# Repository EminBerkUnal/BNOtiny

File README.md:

BNOtiny Breakout Board
------------------------------
Issued Date: 28 November 2023
Revision 1

This is a breakout board that I designed for a BNO08X MEMs sensor. I have designed this board to have the minimal amount of footprint possible. Board size is 48.5mm x 7.0mm.

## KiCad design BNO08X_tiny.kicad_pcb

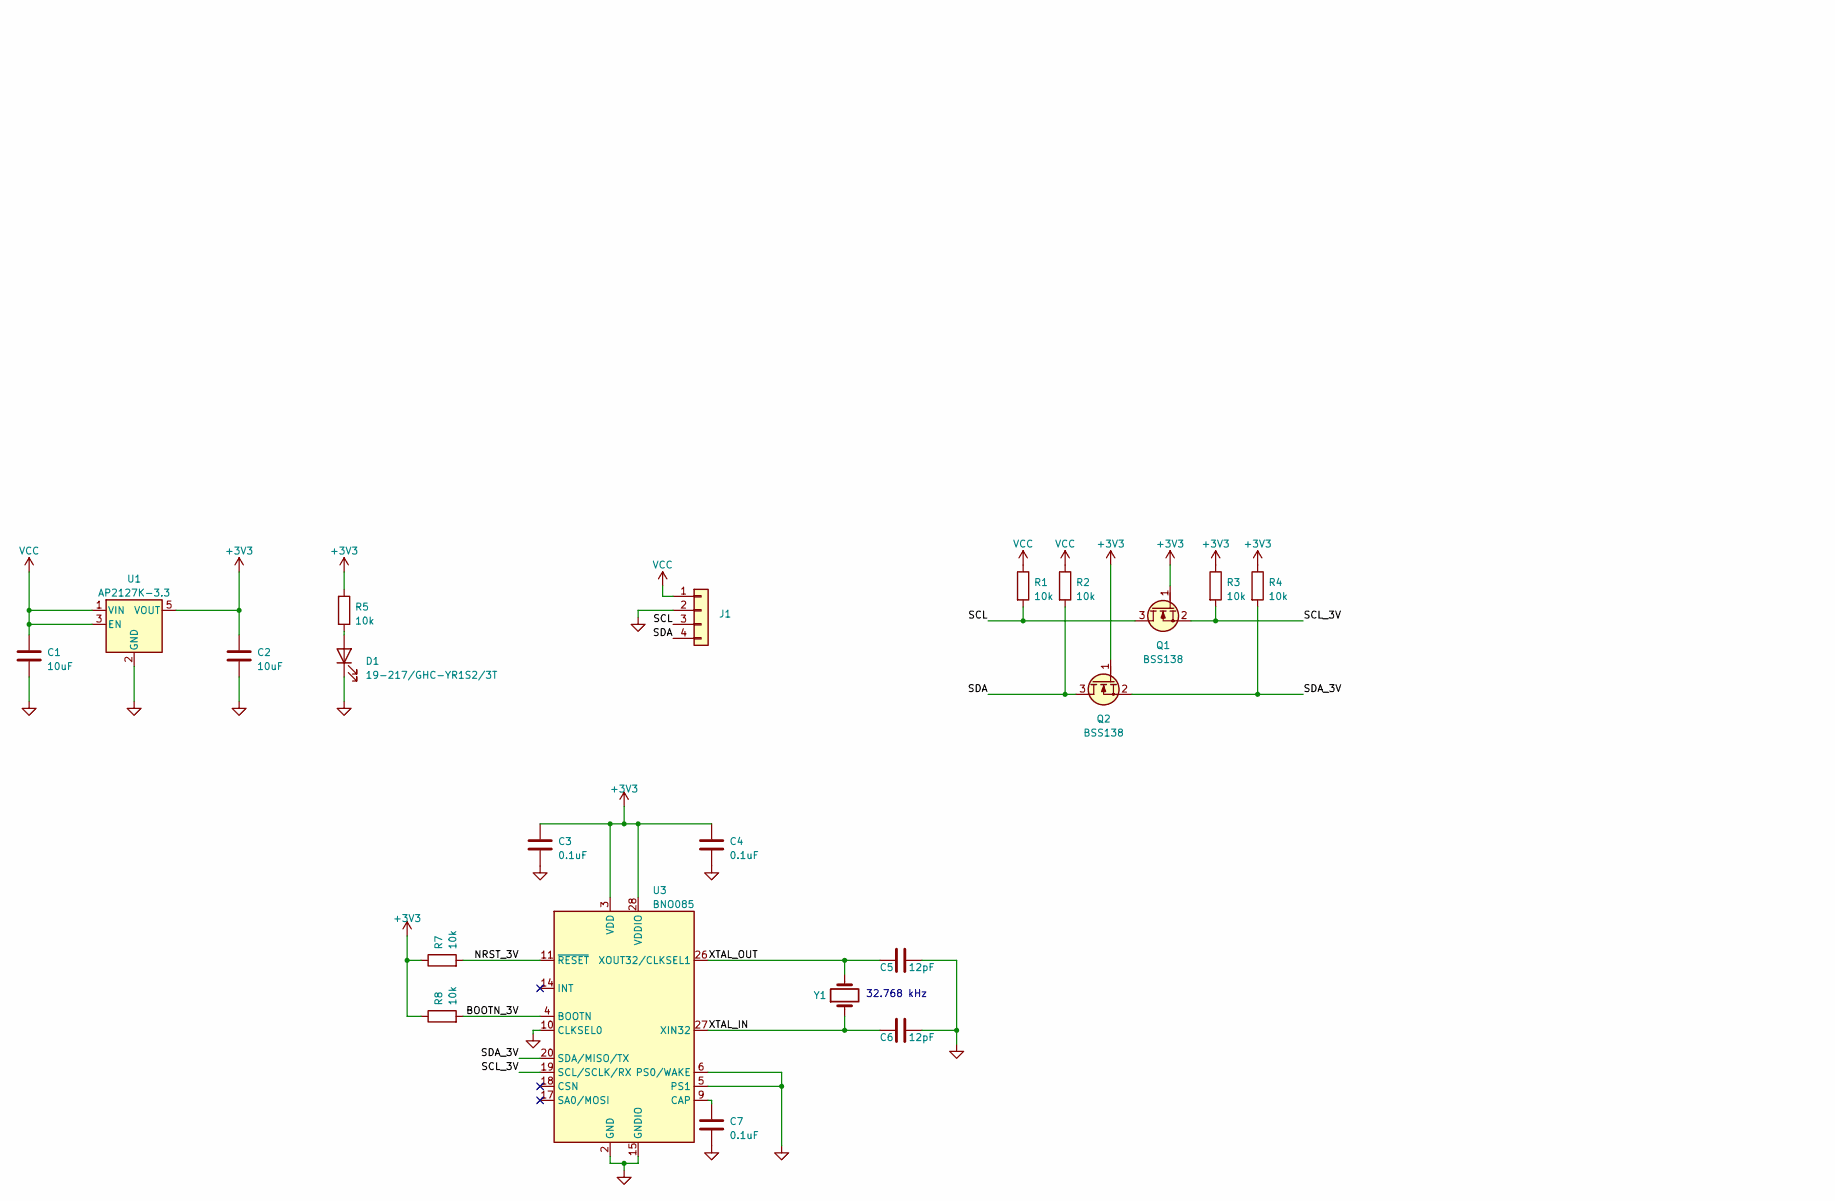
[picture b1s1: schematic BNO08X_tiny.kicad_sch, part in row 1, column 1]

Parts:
C1, C2: 10uF; C_0402_1005Metric
C3, C4, C7: 0.1uF; C_0402_1005Metric
C5, C6: 12pF; C_0402_1005Metric
D1: 19-217/GHC-YR1S2/3T; LED_0603_1608Metric
J1: Conn_01x04; PinHeader_1x04_P2.54mm_Horizontal
Q1, Q2: BSS138; SOT-23
R1, R2, R3, R4, R5, R7, R8: 10k; R_0402_1005Metric
U1: AP2127K-3.3; SOT-23-5
U3: BNO085; LGA-28_5.2x3.8mm_P0.5mm
Y1: Q13FC1350000400; Crystal_SMD_3215-2Pin_3.2x1.5mm

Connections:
+3V3: C2.1, C3.1, C4.1, Q1.1 (G), Q2.1 (G), R3.1, R4.1, R5.1, R7.1, R8.1, U1.5 (VOUT), U3.3 (VDD), U3.28 (VDDIO)
/BOOTN_3V: R8.2, U3.4 (BOOTN)
/NRST_3V: R7.2, U3.11 (~RESET)
/SCL: J1.3, Q1.3 (D), R1.2
/SCL_3V: Q1.2 (S), R3.2, U3.19 (SCL/SCLK/RX)
/SDA: J1.4, Q2.3 (D), R2.2
/SDA_3V: Q2.2 (S), R4.2, U3.20 (SDA/MISO/TX)
/XTAL_IN: C6.2, U3.27 (XIN32), Y1.1
/XTAL_OUT: C5.2, U3.26 (XOUT32/CLKSEL1), Y1.2
GND: C1.2, C2.2, C3.2, C4.2, C5.1, C6.1, C7.2, D1.1 (K), J1.2, U1.2 (GND), U3.2 (GND), U3.5 (PS1), U3.6 (PS0/WAKE), U3.10 (CLKSEL0), U3.15 (GNDIO), U3.16 (GNDIO), U3.25 (GNDIO)
unnamed: D1.2 (A), R5.2
unnamed: C7.1, U3.9 (CAP)
VCC: C1.1, J1.1, R1.1, R2.1, U1.1 (VIN), U1.3 (EN)

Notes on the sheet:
32.768 kHz
Referance Design

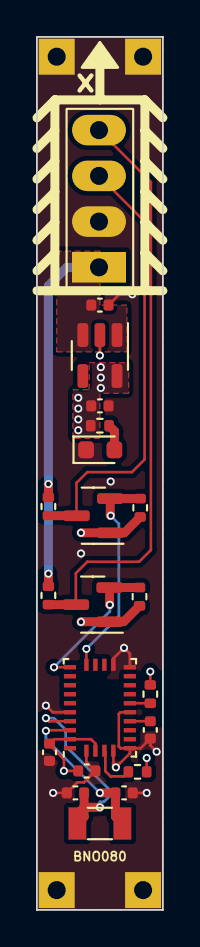
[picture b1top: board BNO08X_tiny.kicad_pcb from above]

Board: 4 copper layers, 7.0 x 48.5 mm, 21 parts (0 on the bottom side), 13 nets.
